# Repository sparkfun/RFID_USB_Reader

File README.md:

SparkFun RFID USB Reader
=========================

[*SparkFun RFID USB Reader (SEN-09963)*](https://www.sparkfun.com/products/9963)

The SparkFun RFID USB Reader is a simple to use, USB to serial base unit for the ID-3LA, ID-12LA, and ID-20LA readers.

Documentation
-------------
- **[Hookup Guide](https://learn.sparkfun.com/tutorials/sparkfun-rfid-starter-kit-hookup-guide)** - The hookup guide for the SparkFun RFID USB Reader

Repository Contents
-------------------
- **[/Hardware](/Hardware/)** - Hardware design files (.brd, .sch)
- **[/Production](/Production/)** - Production files

Product Variants
----------------
- [SEN-28020](https://www.sparkfun.com/sparkfun-rfid-usb-c-reader.html) - USB-C connector and CH340C converter
- [SEN-09963](https://www.sparkfun.com/sparkfun-rfid-usb-reader.html) - Original product *(w/ USB mini-B connector and FTDI converter)*

Version History
---------------
- [v10](https://github.com/sparkfun/RFID_USB_Reader/releases/tag/v10) - Initial Release

License Information
-------------------

This product is ***open source***!

Please review the [`LICENSE.md`](./LICENSE.md) file for license information.

If you have any questions or concerns about licensing, please contact technical support on our [SparkFun forums](https://forum.sparkfun.com/viewforum.php?f=152).

Distributed as-is; no warranty is given.

- Your friends at SparkFun.

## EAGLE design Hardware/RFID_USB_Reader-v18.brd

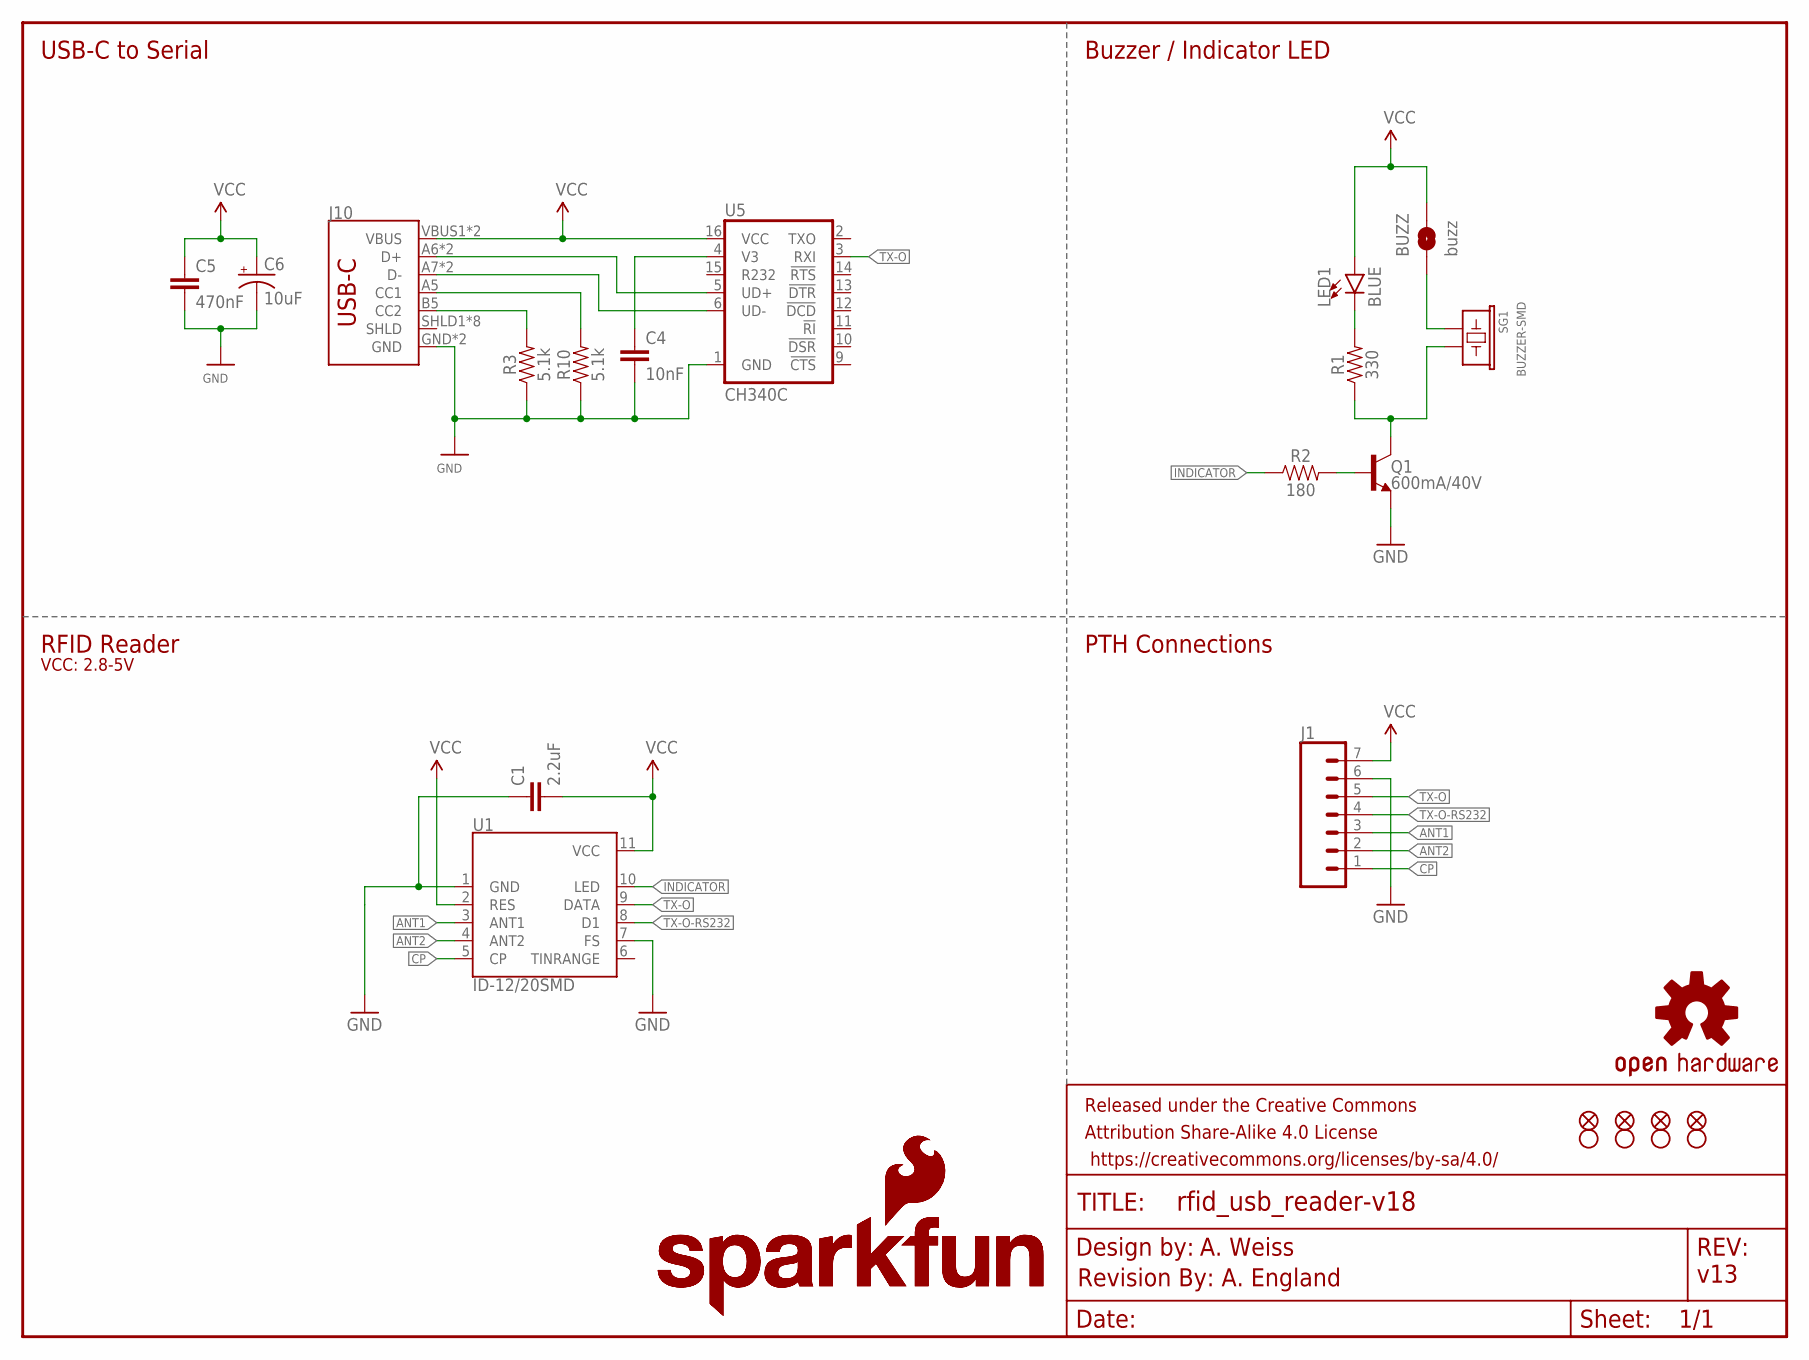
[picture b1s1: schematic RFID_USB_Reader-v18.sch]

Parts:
BUZZ: buzz; SMT-JUMPER_2_NO_NO-SILK
C1: 2.2uF; 0603
C4: 10nF; 0603
C5: 470nF; 0603
C6: 10uF; 0603-POLAR
FRAME1: FRAME-LETTER; CREATIVE_COMMONS
J1: CONN_07; 1X07
J10: USB_C2-LAYER; USB-C-16P
JP1, JP2, JP3, JP5: FIDUCIAL1X2; FIDUCIAL-1X2
LED1: BLUE; LED-0603
LOGO1, LOGO2: SFE_LOGO_NAME_FLAME.1_INCH; SFE_LOGO_NAME_FLAME_.1
LOGO3: OSHW-LOGOS; OSHW-LOGO-S
LOGO4: REVISION
Q1: 600mA/40V; SOT23-3
R1: 330; 0603
R2: 180; 0603
R3, R10: 5.1k; 0603
SG1: BUZZER-SMD; BUZZER-CCV
U1: ID-12/20SMD; ID-12_SMD
U5: CH340C; SO016
U$4, U$5, U$6, U$7: STAND-OFF

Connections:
ANT1: J1.3, U1.3 (ANT1)
ANT2: J1.2, U1.4 (ANT2)
CP: J1.1, U1.5 (CP)
GND: C1.1, C4.2, C5.2, C6.-, J1.6, J10.GND, J10.GND2 (GND), Q1.2 (E), R3.1, R10.1, U1.1 (GND), U1.7 (FS), U5.1 (GND)
INDICATOR: R2.1, U1.10 (LED)
unnamed: Q1.3 (C), R1.1, SG1.- (2)
unnamed: C4.1, U5.4 (V3)
unnamed: J10.A6 (D+), J10.B6 (D+), U5.5 (UD+)
unnamed: BUZZ.1, SG1.+ (1)
unnamed: J10.A5 (CC1), R10.2
unnamed: LED1.C, R1.2
unnamed: Q1.1 (B), R2.2
unnamed: J10.A7 (D-), J10.B7 (D-), U5.6 (UD-)
unnamed: J10.B5 (CC2), R3.2
TX-O: J1.5, U1.9 (DATA), U5.3 (RXI)
TX-O-RS232: J1.4, U1.8 (D1)
VCC: BUZZ.2, C1.2, C5.1, C6.+, J1.7, J10.VBUS1 (VBUS), J10.VBUS2 (VBUS), LED1.A, U1.2 (RES), U1.11 (VCC), U5.16 (VCC)

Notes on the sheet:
A. Weiss
A. England
v13
RFID Reader
USB-C to Serial
Buzzer / Indicator LED
PTH Connections
VCC: 2.8-5V

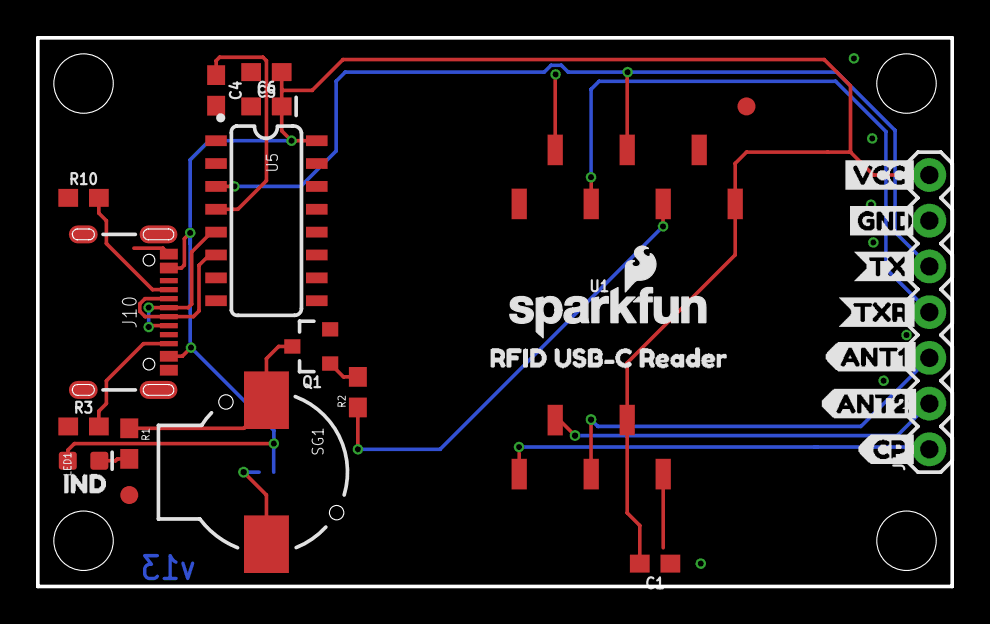
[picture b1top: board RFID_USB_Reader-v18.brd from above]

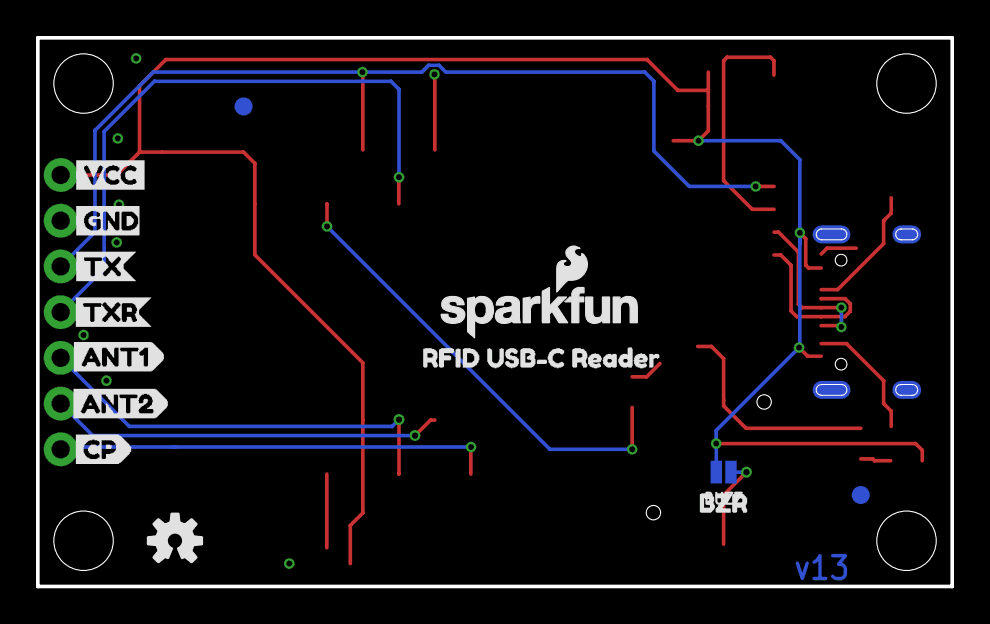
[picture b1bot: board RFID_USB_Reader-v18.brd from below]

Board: 2 copper layers, 50.8 x 30.5 mm, 47 parts (14 on the bottom side), 17 nets.

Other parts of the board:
U$1: CP5
U$3, U$13: GND1
U$8: BZR3
U$9: TX3
U$10: TXR4
U$11, U$12: VCC0
U$14: TX0
U$15: TXR1
U$16: CP2
U$17, U$18: RFID_USB#C_READER0
U$19: ANT11
U$20: ANT13
U$21: ANT22
U$22: ANT24
U$23: IND0

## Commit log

2015-03-10 Adding hardware files, updating README
2019-12-05 revising to move plane and routing out from underneath of RFID reader, removing ant pin breakout
2019-12-06 post checklist changes
2019-12-06 post review changes
2019-12-09 post QC checklist changes
2019-12-09 changing name to USB-C
2019-12-17 updating Buzzer and npn transistor to have PROD_ID
2025-01-09 v20 Ready for Review
    - Move design to KiCad
    - Push all connectors to one side of the board
    - Round dimensions to nearest 0.25"
    - Update to USB-C
    - Swap out FTDI for CH340
    - Center RFID module in 1" CTC mounting holes
2025-01-10 Get rid of backups
2025-01-10 Update to small symbols. Add RFID outline device.
2025-01-10 Add fiducials. Add logos. Letter size.
2025-01-10 Add 3D models
2025-01-10 Rename files
2025-01-21 Center USB-C Connector
    - Move USB-C connector to center
    - Arrange 0.1" headers to either side
2025-01-21 Move fiducial from silk. Add version in copper. Move OSHW gear from silk.
2025-01-21 Reduce to two layer board
2025-01-21 Add panel files
2025-01-21 Align silk labels
2025-01-21 Change decoupling cap. Change LED resistor.
2025-01-21 Fix DRC error
2025-01-23 Change to PTH connectors
2025-02-05 Post design review fixes
2025-02-05 Remove old files.
2025-03-14 Link hookup guide
2025-03-20 Update template files
2025-03-20 Update README.md
    Update file format
    Add new product variant

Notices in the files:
parts and their libraries:
SparkFun-IC-Comms: Licensing: Creative Commons ShareAlike 4.0 International - https://creativecommons.org/licenses/by-sa/4.0
SparkFun-Aesthetics: Released under the Creative Commons Attribution Share-Alike 4.0 License
SparkFun-Aesthetics: https://creativecommons.org/licenses/by-sa/4.0
